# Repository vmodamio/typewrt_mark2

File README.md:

# Typewrt Mark II (ver 2.0)

Typewrt is a modern conception of a digital typewriter, designed as an
instrument for creating literary works without the need of further devices or
software. 
The idea revolves around a mechanical feeling, and it is designed with the
following key aspects:
1) Output: A reflective memory-in-pixel monochrome LCD from SHARP. This is a
4.4" display with a todays low resolution (320x240, QVGA). This resolution is 
enough to produce sharp glyphs using VGA font 8x16 bitmaps. It allows for 15
lines with 40 characters. The readability is exceptional both indoors and
outdoors. Because of the resolution and the ability to perform partial
refreshes, it updates very fast. 

2) Input: A mechanical keyboard with high quality switches and thick PBT
keycaps, arranged in a 60% layout. Mounted in a sturdy brass plate and a custom
made PCB. 
4) Power: Typewrt doesn't produce light. It doesn't stress the eyes. It doesn't
produce heat when you write on the lap. And it does not need a charger around.
The SHARP display is ultra low power. As it does the keyboard and the main
board. 
3) Process: The core of the device, and the main departure from a typewriter or 
a simple drafting device. Typewrt is an embedded vi text editor. It allows to
navigate through the document or documents very efficiently. Manipulate text
with any complexity, and recursively. Do search and replace, etc. You can even
autocomplete words, or perform fuzzy searches. It works natively with utf-8
encoding, and it can change the keyboard layout on the fly to english, spanish,
italian, french, german, norwegian, turkish and colemak.
5) Ergonomics: The design is meant to be robust and stable. The keyboard height
has been minimized. Cherry profile keycups are used, and the keyboard plane is
tilted by 6 degree.  The display distance and viewing angle is kept large
enough to allow long writing sessions. The display is 35 degree respect to the 
horizontal plane. The keyboard has been silenced as much as possible, so you
have a good peace of mind when typing in public places.  The tactility and
response of the keyboard is very conforting. 
6) Remote sync: The device has LE Bluetooth and allows to copy your files to
your phone consuming very little power, and without needing external networks.

The main difference of Typewrt mark II respect to the first iteration is the
hardware. Typewrt-I was built with a single-board-computer, running a ARM based 
linux from which you could run any program on the terminal. 
Typewrt-II doesn't have a computer. There is no terminal or specific drivers for
the keyboard or the display. Keyboard, display and text processor conform a
unique firmware embedded into a ESP32S3 microprocessor. 
Just one application (a modified vi editor with a simple file browser), running 
in a much more constrained environment. 8 MB of ram memory instead of 0.5 GB in
Typewrt-I. 1 MB firmware on flash memory instead of 0.5GB of linux distribution. 
And still, it performs faster, and consumes much less power. 
The interaction with Typewrt-2 is straight. There is no loggins or shells or
passwords. You press the power button and start writing instant on a blank 
document.

# How to:
Because the esp firmware is a submodule repository, clone this project as 
``` 
git clone --recurse-submodules https://github.com/vmodamio/typewrt_mark2.git 
```
The building process might be a long project. Please dont hesitate to ask if you
find difficulties and/or lack of documentation. 
For flashing the firmware, you need the Espressiff IDF installed in your computer.
You can follow [the instructions here for the v6.0](https://docs.espressif.com/projects/esp-idf/en/v6.0.1/esp32s3/get-started/index.html)
Once installed, from the /firmware/esp folder:
``` 
idf.py build
idf.py flash
```

# Firmware:
The text editor has been forked from the [fantastic nextVi](https://github.com/kyx0r/nextvi) 
text editor by Kyryl Melekhin. The editor, originally a terminal program, has been 
adapted to an embedded firmware using the Espressiff IDF, and it runs under FreeRTOS. 
Regarding functionality, the original right-to-left support, all the syntax highlight and 
filetype code, as well as all shell/terminal related code has been removed. 
The program has been adapted to a non-terminal environment, with a custom
keyboard and display interpretation. Additionally, all the functionality related to
files, paths or filesystem in general, has been derived to a more-dedicated filebrowser. 
The filebrowser is in fact the place where you land with the former quit command. 
A battery, memmory and date/time status has been added, as well as a BLE small protocol 
to transfer files.  And last, an special hard-wrap mechanism has been implemented.  

# Hardware:
The machine consists on a feather ESP32s3[d] (unexpected maker) and an Adafruit
adalogger RTC+SD card. The Sharp MIP 4.4" display, is mounted in a custom PCB
that has a 5V booster, and a 7555 timer for the vcom signal (both ultra low
power). The keyboard pcb consists barely on an octal latch SN74HC573A that
drives 8 inputs/outputs. In addition, a power button and a yellow led on the 
enclosure, and a usb-c connector on the back. For the connector, a tiny pcb was
made to pull down the CC1 and CC2 lines with 5.1k. It has also a small jumper to
remove the data lines, in case you dont want someone touching your firmware. 

# Power figures:
Typewrt main display, the SHARP MIP, consumes 50 uA when idle, and 600 uA when
refreshing. It is probably the lowest power display ever. This, considering
that, in many writing divices, the display is by far the most power hungry part.
The keyboard on Typewrt mark I was implemented on a low power STM32
microcontroller, working in interrupt mode and sleeping most of the time, and
sending via uart events. Typewrt mark II is just one microcontroller, doing
exactly the same task as for the keyboard, but for the whole firmware. 
The display vcom signal is hardware produced with the timer, so no task is
needed for the display when the system is idle.
Check the power consumption folder for real measurements.
Machine idle is around 1.4 mA, typing costs 38 mA, and deep sleep 340 uA.

# Vi at a glance:

Vi is one of the main text editors in unix/linux distributions. Its
functionality is divided into three different modes: insert, nomal and ex mode.
Once you are inside vi, you press "i" to enter insert mode, and you can start
typing in your document. Many people hate vi just because this initial
frustration, akwardness responses of the keyboard when you are not in Insert
mode. This is because vi is very powerful. It has many key bindings, and the
learning curve is somehow step. 

In insert mode, it behaves like the simplest text editor you could imagine. As
far as you dont escape, pressing the Esc key, you basically insert characters
in your text buffer. There are very few but useful key bindings in insert mode
however. Press Ctrl-W to delete your last word. Or Ctrl-N to autocomplete a
word you started typing.  To save your text (to write your buffer into a file),
you escape to enter normal mode, then you type ":" to enter ex mode, and "w
<filename>" to write.

Normal mode is where things get fun. In this mode you dont create text by
typing, but instead you type keybindings to manipulate the text you already
have, or navigate throw the buffer/buffers, copy or paste pieces of text into
the buffer, or different registers, search or replace, delete, and many other
things. This editor paradigm works very nice for coding, among other things,
were you would spend considerable part of your time rearranging pieces of text
or modifying functions or variables. For writing fiction I find it equally
useful.  The navigation, or movements, are the first step departing from your
standard, plain editor. The left, right, up and down cursor movements in vi are
arranged in the main keyboard row as h,j,k,l for left, down, up and right. 
That is the main reason you would't need arrow keys in a vi text editor. 
If you get used to this, you wont miss again the arrow keys.  You can move
forward or backwards by words, paragraphs, programmed marks, entire
documents/buffers.
You can concatenate actions with movements, like delete 5 words backwards, or
find character <character> 3 times, to say, or copy text til mark, or
paste register 1...  Pressing "." in normal mode executes the last instruction
again. For example "dB" to delete backwards  to the begining of a word
(including punctuation). Then pressing "." will continue to delete that way.

# Credits:
The text editor is based on the nextVI project (please refer to the firmware folder).
The VGA font is borrowed from the ZAP group, Australia (Copyright (C) 2004–26, John Zaitseff).
The font used for the splash screen is MomoTrustDisplay-Regular.ttf (Google fonts) 
designed by Type Associates, Copyright 2024 The MoMo Trust Display Project Authors. 

# License:
This project is distributed under GPL3 license. Copyright (C) 2026 Victor Modamio

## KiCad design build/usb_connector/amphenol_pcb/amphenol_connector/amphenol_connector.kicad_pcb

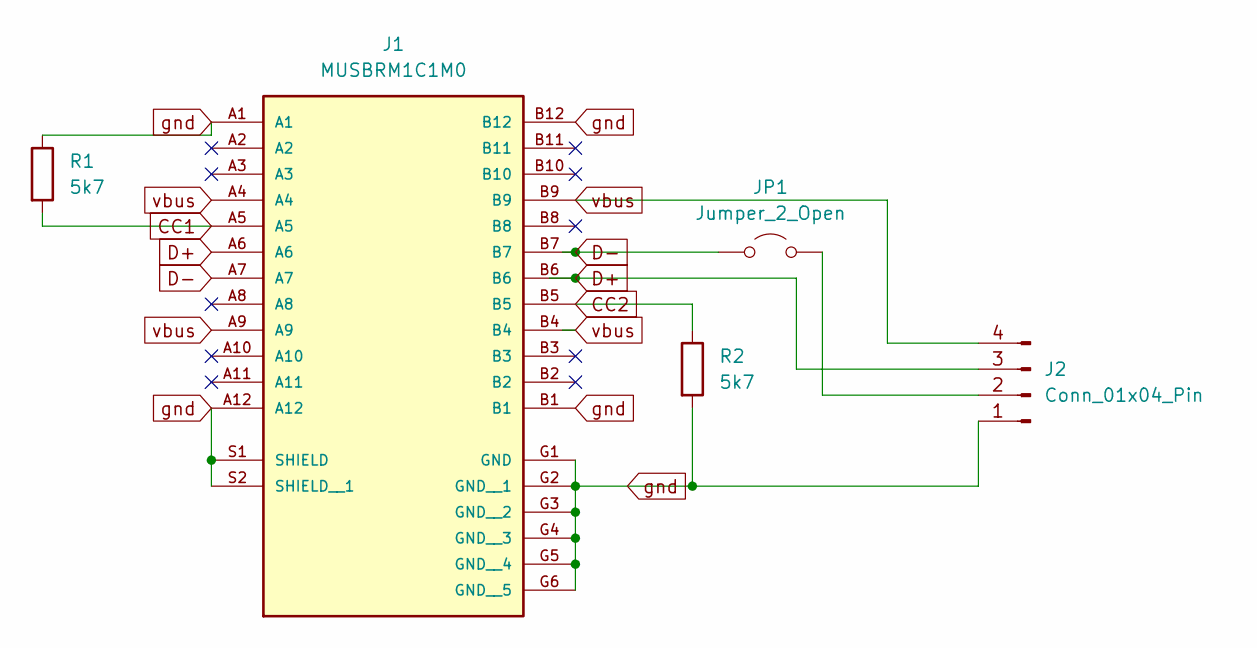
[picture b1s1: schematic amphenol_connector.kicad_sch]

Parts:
J1: MUSBRM1C1M0; AMPHENOL_MUSBRM1C1M0_no_courtyard; PARTREV D
J2: Conn_01x04_Pin; PinHeader_1x04_P1.27mm_Vertical
JP1: Jumper_2_Open; PinHeader_1x02_P1.27mm_Vertical
R1, R2: 5k7; R_1206_3216Metric_Pad1.30x1.75mm_HandSolder

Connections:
CC1: J1.A5, R1.2
CC2: J1.B5, R2.1
D+: J1.A6, J1.B6, J2.3
D-: J1.A7, J1.B7, JP1.1 (A)
unnamed: J2.2, JP1.2 (B)
gnd: J1.A1, J1.A12, J1.B1, J1.B12, J1.G1 (GND), J1.G2 (GND__1), J1.G3 (GND__2), J1.G4 (GND__3), J1.G5 (GND__4), J1.G6 (GND__5), J1.S1 (SHIELD), J1.S2 (SHIELD__1), J2.1, R1.1, R2.2
vbus: J1.A4, J1.A9, J1.B4, J1.B9, J2.4

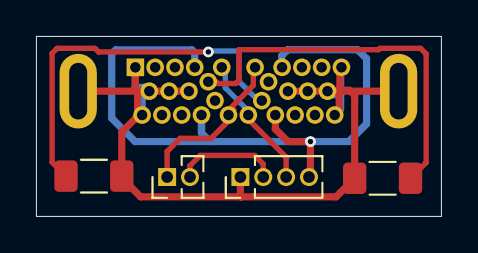
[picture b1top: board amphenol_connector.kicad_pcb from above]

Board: 2 copper layers, 22.5 x 10.0 mm, 5 parts (0 on the bottom side), 7 nets.

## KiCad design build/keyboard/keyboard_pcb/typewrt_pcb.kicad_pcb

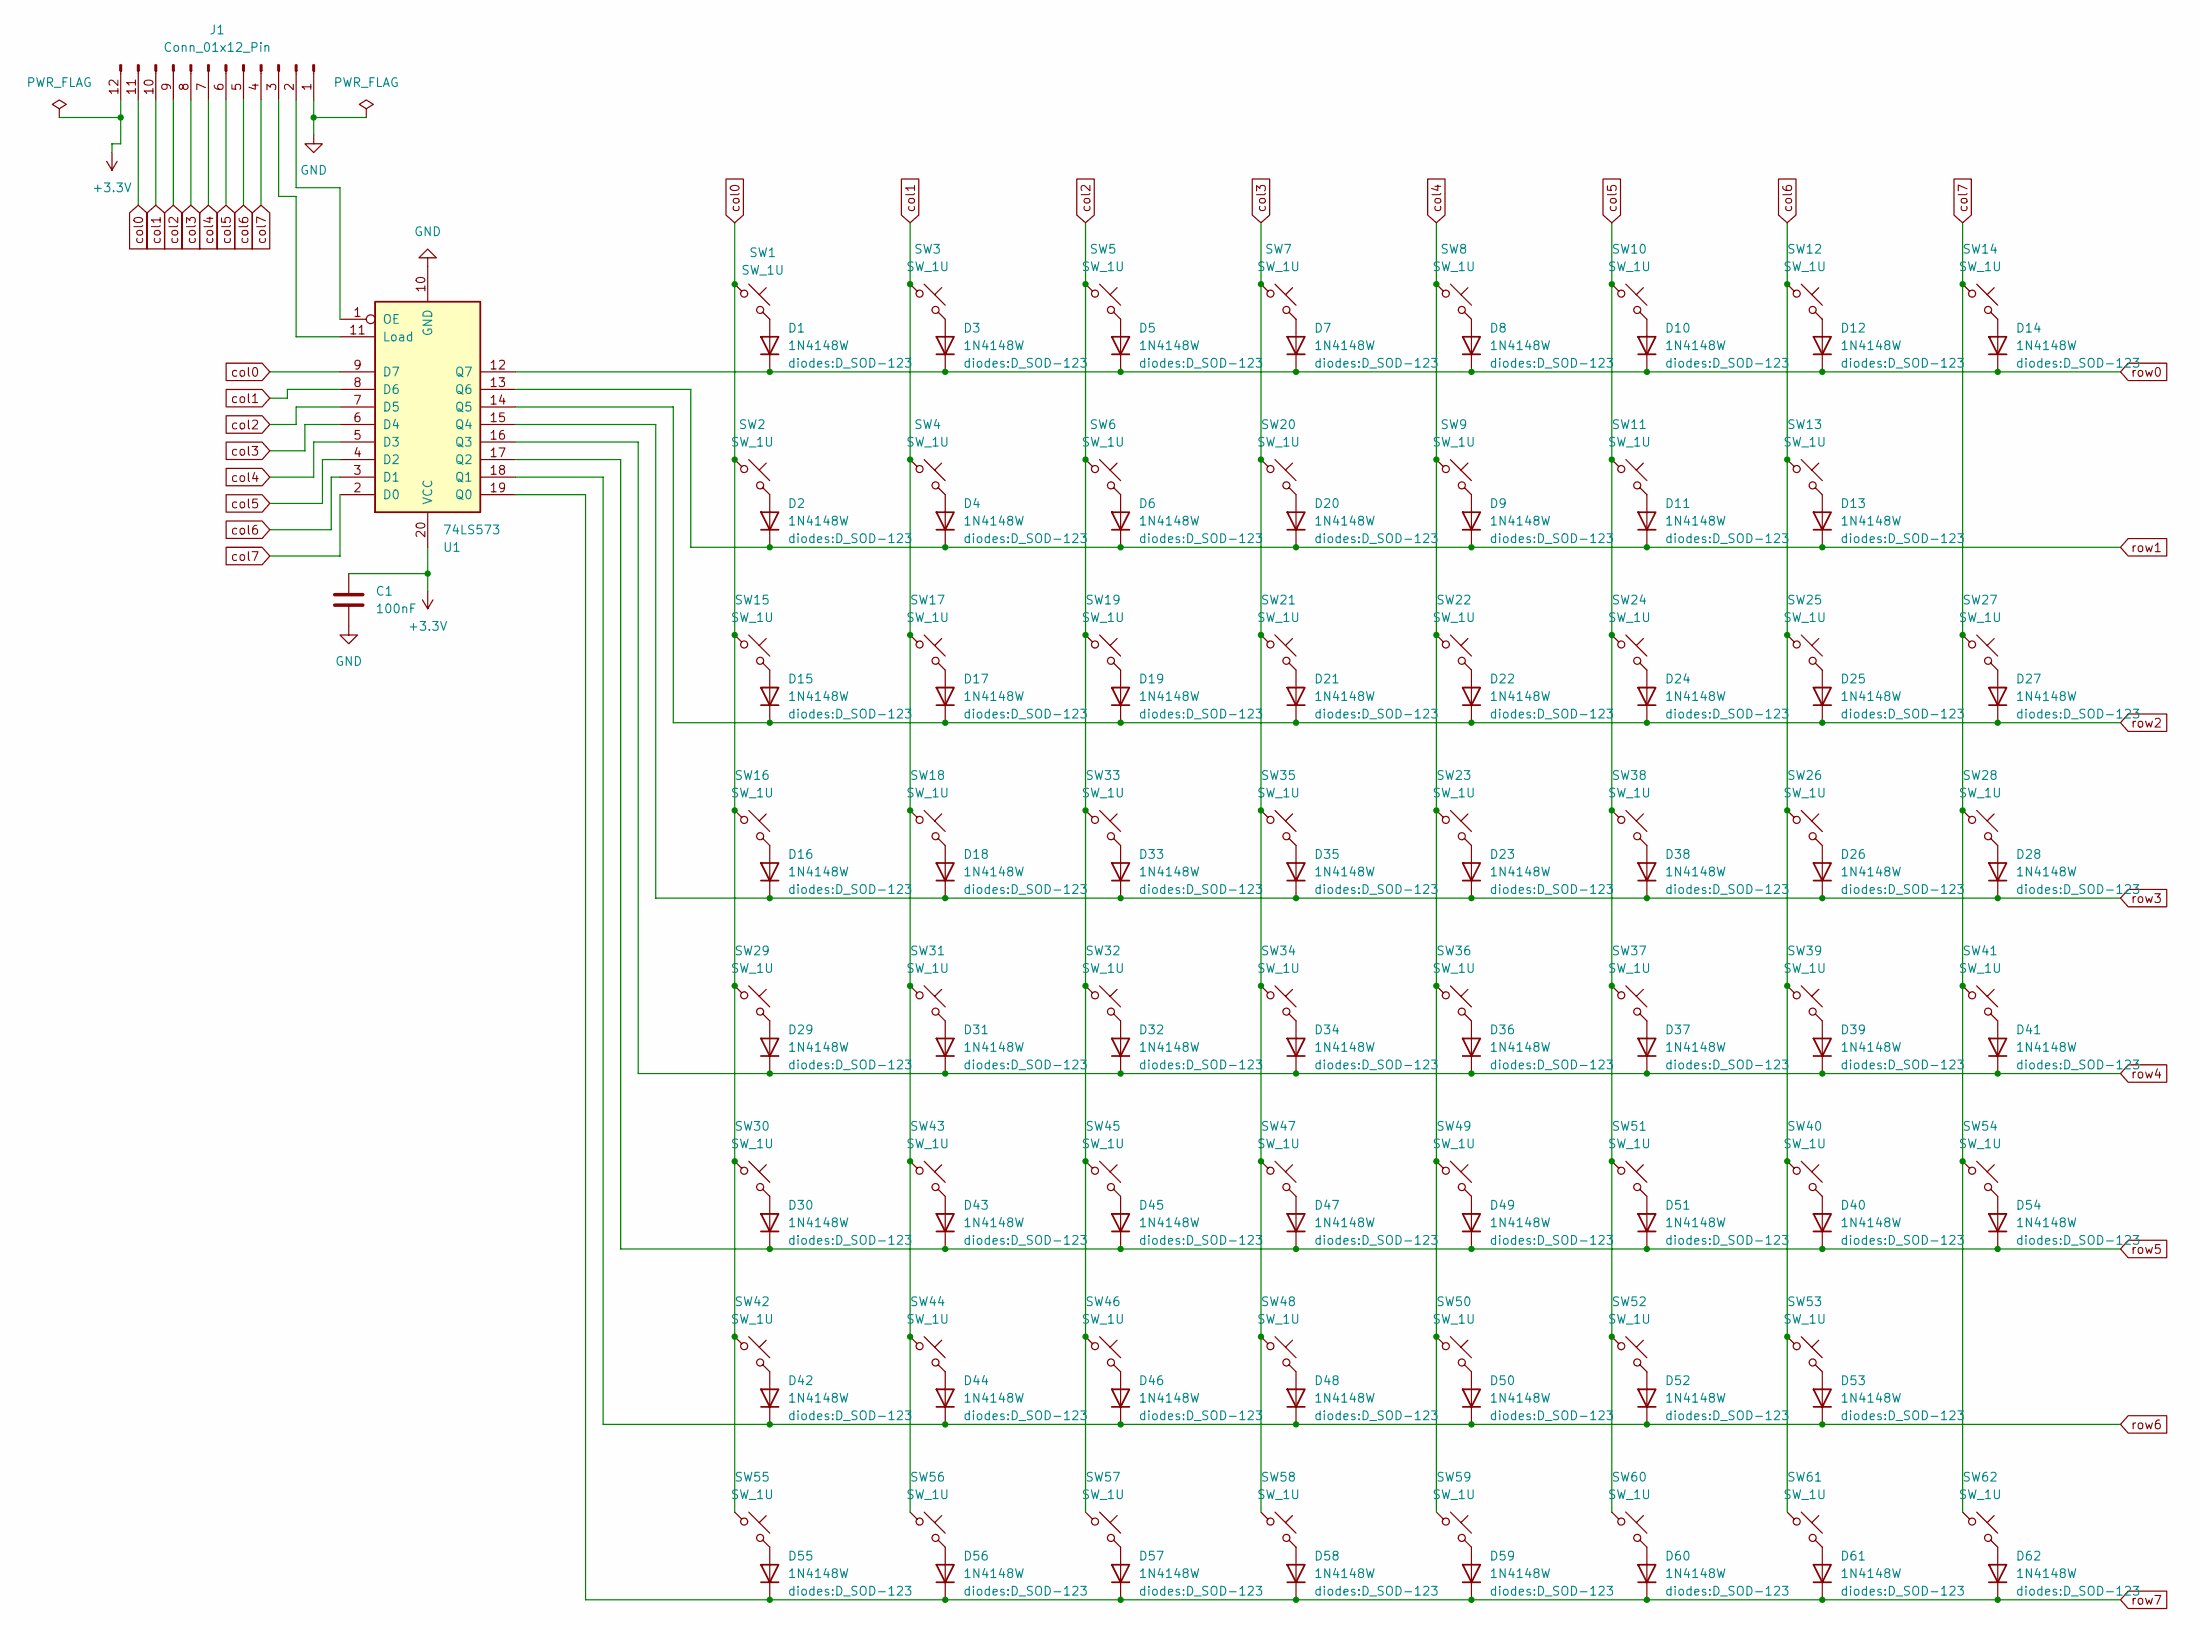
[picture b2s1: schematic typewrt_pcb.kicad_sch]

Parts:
C1: 100nF; C_1206_3216Metric_Pad1.33x1.80mm_HandSolder
D1, D2, D3, D4, D5, D6, D7, D8, D9, D10, D11, D12, D13, D14, D15, D16, D17, D18, D19, D20, D21, D22, D23, D24, D25, D26, D27, D28, D29, D30, D31, D32, D33, D34, D35, D36, D37, D38, D39, D40, D41, D42, D43, D44, D45, D46, D47, D48, D49, D50, D51, D52, D53, D54, D55, D56, D57, D58, D59, D60, D61, D62: 1N4148W; D_SOD-123
J1: Conn_01x12_Pin; PinHeader_1x12_P1.27mm_Vertical
SW1, SW2, SW3, SW4, SW5, SW6, SW7, SW8, SW9, SW10, SW11, SW12, SW13, SW16, SW17, SW18, SW19, SW20, SW21, SW22, SW23, SW24, SW25, SW26, SW27, SW30, SW31, SW32, SW33, SW34, SW35, SW36, SW37, SW38, SW39, SW40, SW41, SW43, SW44, SW45, SW46, SW47, SW48, SW49, SW50, SW51, SW52, SW53: SW_1U; MX-Solderable-1U
SW14: SW_1U; MX-Solderable-2U
SW15: SW_1U; MX-Solderable-1.5U
SW28: SW_1U; MX-Solderable-ISO
SW29: SW_1U; MX-Solderable-1.75U
SW42, SW55, SW56, SW57, SW59, SW60, SW61, SW62: SW_1U; MX-Solderable-1.25U
SW54: SW_1U; MX-Solderable-2.75U
SW58: SW_1U; MX-Solderable-6.25U-ReversedStabilizers
U1: 74LS573; DIP-20_W7.62mm

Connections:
+3.3V: C1.1, J1.12, U1.20 (VCC)
GND: C1.2, J1.1, U1.10 (GND)
unnamed: D1.2 (A), SW1.2
unnamed: D2.2 (A), SW2.2
unnamed: D3.2 (A), SW3.2
unnamed: D4.2 (A), SW4.2
unnamed: D5.2 (A), SW5.2
unnamed: D6.2 (A), SW6.2
unnamed: D7.2 (A), SW7.2
unnamed: D8.2 (A), SW8.2
unnamed: D9.2 (A), SW9.2
unnamed: D10.2 (A), SW10.2
unnamed: D11.2 (A), SW11.2
unnamed: D12.2 (A), SW12.2
unnamed: D13.2 (A), SW13.2
unnamed: D14.2 (A), SW14.2
unnamed: D15.2 (A), SW15.2
unnamed: D16.2 (A), SW16.2
unnamed: D17.2 (A), SW17.2
unnamed: D18.2 (A), SW18.2
unnamed: D19.2 (A), SW19.2
unnamed: D20.2 (A), SW20.2
unnamed: D21.2 (A), SW21.2
unnamed: D22.2 (A), SW22.2
unnamed: D23.2 (A), SW23.2
unnamed: D24.2 (A), SW24.2
unnamed: D25.2 (A), SW25.2
unnamed: D26.2 (A), SW26.2
unnamed: D27.2 (A), SW27.2
unnamed: D28.2 (A), SW28.2
unnamed: D29.2 (A), SW29.2
unnamed: D30.2 (A), SW30.2
unnamed: D31.2 (A), SW31.2
unnamed: D32.2 (A), SW32.2
unnamed: D33.2 (A), SW33.2
unnamed: D34.2 (A), SW34.2
unnamed: D35.2 (A), SW35.2
unnamed: D36.2 (A), SW36.2
unnamed: D37.2 (A), SW37.2
unnamed: D38.2 (A), SW38.2
unnamed: D39.2 (A), SW39.2
unnamed: D40.2 (A), SW40.2
unnamed: D41.2 (A), SW41.2
unnamed: D42.2 (A), SW42.2
unnamed: D43.2 (A), SW43.2
unnamed: D44.2 (A), SW44.2
unnamed: D45.2 (A), SW45.2
unnamed: D46.2 (A), SW46.2
unnamed: D47.2 (A), SW47.2
unnamed: D48.2 (A), SW48.2
unnamed: D49.2 (A), SW49.2
unnamed: D50.2 (A), SW50.2
unnamed: D51.2 (A), SW51.2
unnamed: D52.2 (A), SW52.2
unnamed: D53.2 (A), SW53.2
unnamed: D54.2 (A), SW54.2
unnamed: D55.2 (A), SW55.2
unnamed: D56.2 (A), SW56.2
unnamed: D57.2 (A), SW57.2
unnamed: D58.2 (A), SW58.2
unnamed: D59.2 (A), SW59.2
unnamed: D60.2 (A), SW60.2
unnamed: D61.2 (A), SW61.2
unnamed: D62.2 (A), SW62.2
unnamed: J1.2, U1.1 (OE)
unnamed: J1.3, U1.11 (Load)
col0: J1.11, SW1.1, SW2.1, SW15.1, SW16.1, SW29.1, SW30.1, SW42.1, SW55.1, U1.9 (D7)
col1: J1.10, SW3.1, SW4.1, SW17.1, SW18.1, SW31.1, SW43.1, SW44.1, SW56.1, U1.8 (D6)
col2: J1.9, SW5.1, SW6.1, SW19.1, SW32.1, SW33.1, SW45.1, SW46.1, SW57.1, U1.7 (D5)
col3: J1.8, SW7.1, SW20.1, SW21.1, SW34.1, SW35.1, SW47.1, SW48.1, SW58.1, U1.6 (D4)
col4: J1.7, SW8.1, SW9.1, SW22.1, SW23.1, SW36.1, SW49.1, SW50.1, SW59.1, U1.5 (D3)
col5: J1.6, SW10.1, SW11.1, SW24.1, SW37.1, SW38.1, SW51.1, SW52.1, SW60.1, U1.4 (D2)
col6: J1.5, SW12.1, SW13.1, SW25.1, SW26.1, SW39.1, SW40.1, SW53.1, SW61.1, U1.3 (D1)
col7: J1.4, SW14.1, SW27.1, SW28.1, SW41.1, SW54.1, SW62.1, U1.2 (D0)
row0: D1.1 (K), D3.1 (K), D5.1 (K), D7.1 (K), D8.1 (K), D10.1 (K), D12.1 (K), D14.1 (K), U1.12 (Q7)
row1: D2.1 (K), D4.1 (K), D6.1 (K), D9.1 (K), D11.1 (K), D13.1 (K), D20.1 (K), U1.13 (Q6)
row2: D15.1 (K), D17.1 (K), D19.1 (K), D21.1 (K), D22.1 (K), D24.1 (K), D25.1 (K), D27.1 (K), U1.14 (Q5)
row3: D16.1 (K), D18.1 (K), D23.1 (K), D26.1 (K), D28.1 (K), D33.1 (K), D35.1 (K), D38.1 (K), U1.15 (Q4)
row4: D29.1 (K), D31.1 (K), D32.1 (K), D34.1 (K), D36.1 (K), D37.1 (K), D39.1 (K), D41.1 (K), U1.16 (Q3)
row5: D30.1 (K), D40.1 (K), D43.1 (K), D45.1 (K), D47.1 (K), D49.1 (K), D51.1 (K), D54.1 (K), U1.17 (Q2)
row6: D42.1 (K), D44.1 (K), D46.1 (K), D48.1 (K), D50.1 (K), D52.1 (K), D53.1 (K), U1.18 (Q1)
row7: D55.1 (K), D56.1 (K), D57.1 (K), D58.1 (K), D59.1 (K), D60.1 (K), D61.1 (K), D62.1 (K), U1.19 (Q0)

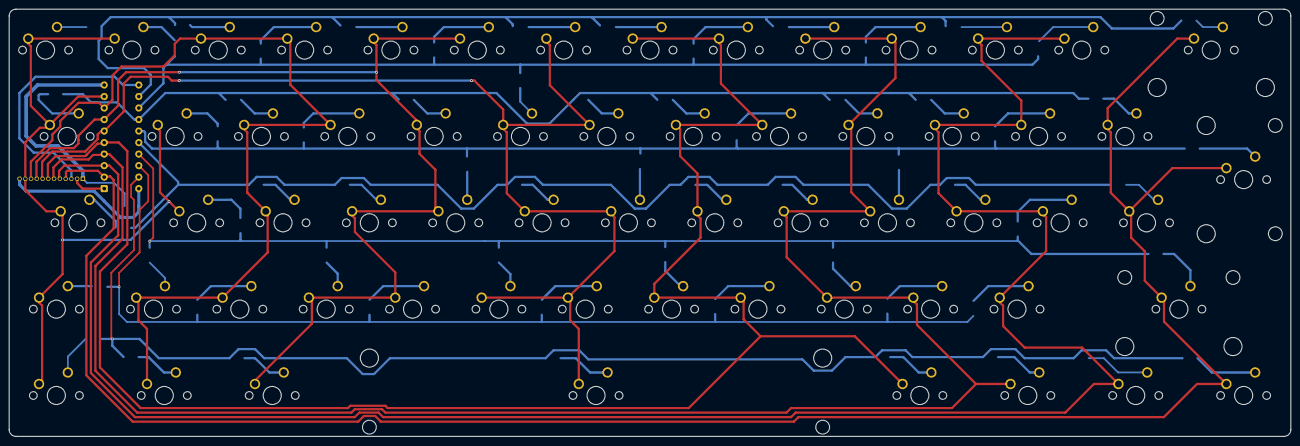
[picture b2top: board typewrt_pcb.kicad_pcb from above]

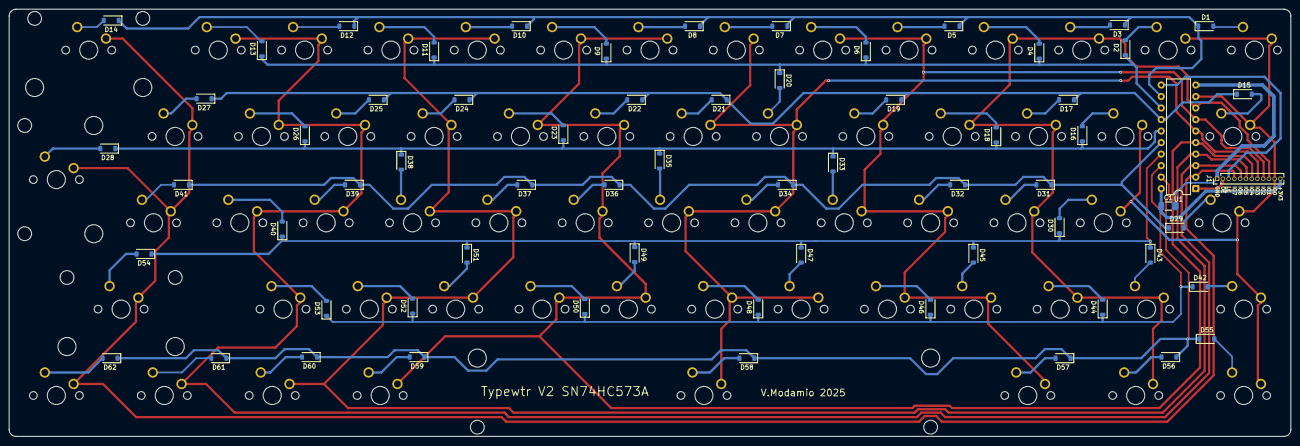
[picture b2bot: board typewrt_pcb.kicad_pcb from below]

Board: 2 copper layers, 282.8 x 94.2 mm, 127 parts (65 on the bottom side), 82 nets.

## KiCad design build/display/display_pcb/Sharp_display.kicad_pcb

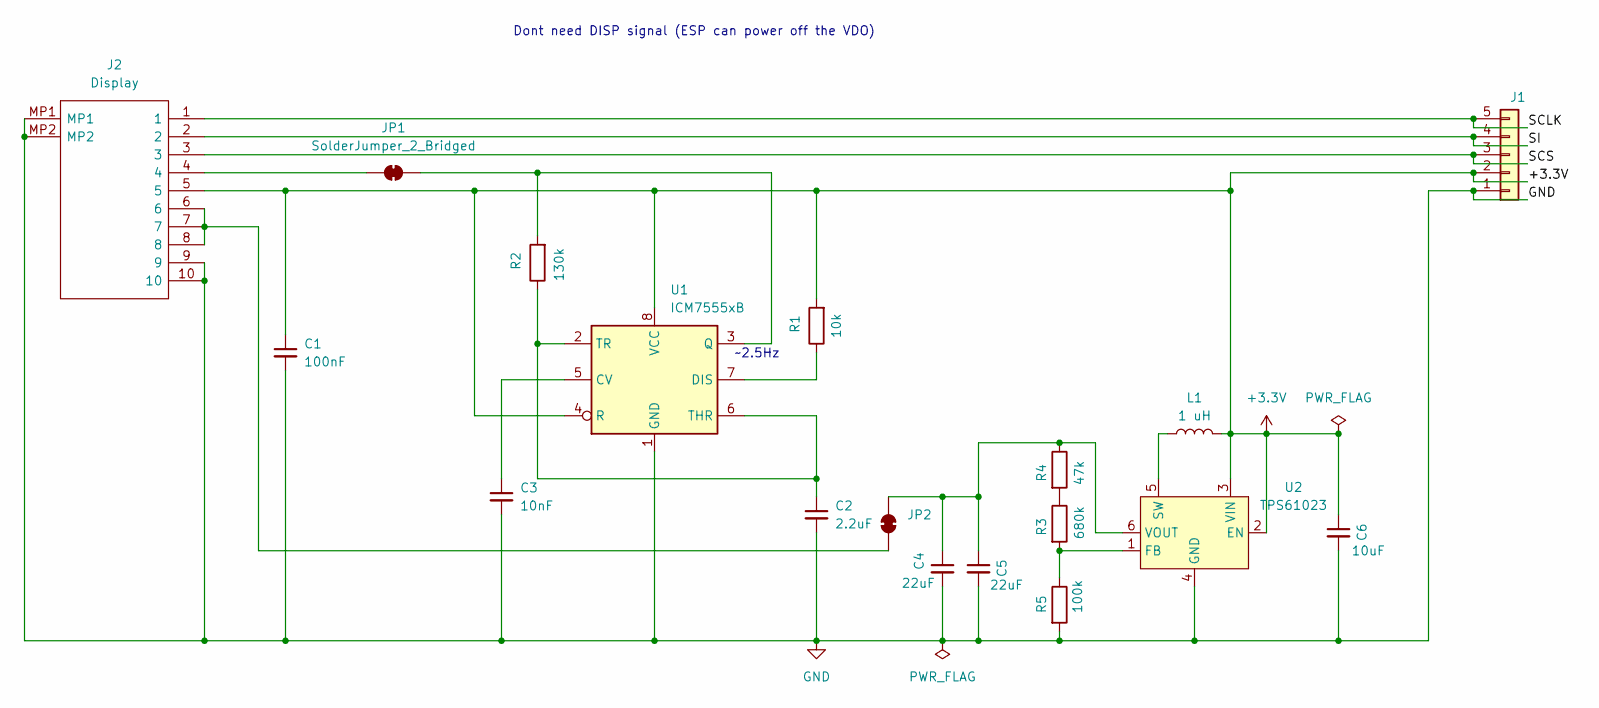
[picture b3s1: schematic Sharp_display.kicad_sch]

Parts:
C1: 100nF; C_1206_3216Metric_Pad1.33x1.80mm_HandSolder
C2: 2.2uF; C_1206_3216Metric_Pad1.33x1.80mm_HandSolder
C3: 10nF; C_1206_3216Metric_Pad1.33x1.80mm_HandSolder
C4, C5: 22uF; C_1206_3216Metric_Pad1.33x1.80mm_HandSolder
C6: 10uF; C_1206_3216Metric_Pad1.33x1.80mm_HandSolder
J1: Conn_01x05; PinHeader_1x05_P2.54mm_Vertical
J2: Display; GCT_FFC2B35-10-G_REVA2; Manufacturer_Part_Number 5051101092; Mouser Part Number N/A
JP1, JP2: SolderJumper_2_Bridged; SolderJumper-2_P1.3mm_Bridged2Bar_Pad1.0x1.5mm
L1: 1 uH; L_Wurth_WE-LQSH-4020
R1: 10k; R_1206_3216Metric_Pad1.30x1.75mm_HandSolder
R2: 130k; R_1206_3216Metric_Pad1.30x1.75mm_HandSolder
R3: 680k; R_1206_3216Metric_Pad1.30x1.75mm_HandSolder
R4: 47k; R_1206_3216Metric_Pad1.30x1.75mm_HandSolder
R5: 100k; R_1206_3216Metric_Pad1.30x1.75mm_HandSolder
U1: ICM7555xB; SOIC127P600X175-8N
U2: TPS61023; SOT-563

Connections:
+3.3V: C1.1, C6.1, J1.2, J2.5, L1.2, R1.2, U1.4 (R), U1.8 (VCC), U2.2 (EN), U2.3 (VIN)
/SCLK: J1.5, J2.1
/SCS: J1.3, J2.3
/SI: J1.4, J2.2
GND: C1.2, C2.2, C3.2, C4.2, C5.2, C6.2, J1.1, J2.9, J2.10, J2.MP1, J2.MP2, R5.2, U1.1 (GND), U2.4 (GND)
unnamed 5: J2.4, JP1.1 (A); also elsewhere on the board
unnamed: JP1.2 (B), R2.2, U1.3 (Q)
unnamed 7: J2.6, J2.7, J2.8, JP2.1 (A); also elsewhere on the board
unnamed: C4.1, C5.1, JP2.2 (B), R4.1, U2.6 (VOUT)
unnamed: R3.1, R4.2
unnamed: C3.1, U1.5 (CV)
unnamed: R1.1, U1.7 (DIS)
unnamed: C2.1, R2.1, U1.2 (TR), U1.6 (THR)
unnamed: R3.2, R5.1, U2.1 (FB)
unnamed: L1.1, U2.5 (SW)

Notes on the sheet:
~2.5Hz
Dont need DISP signal (ESP can power off the VDO)

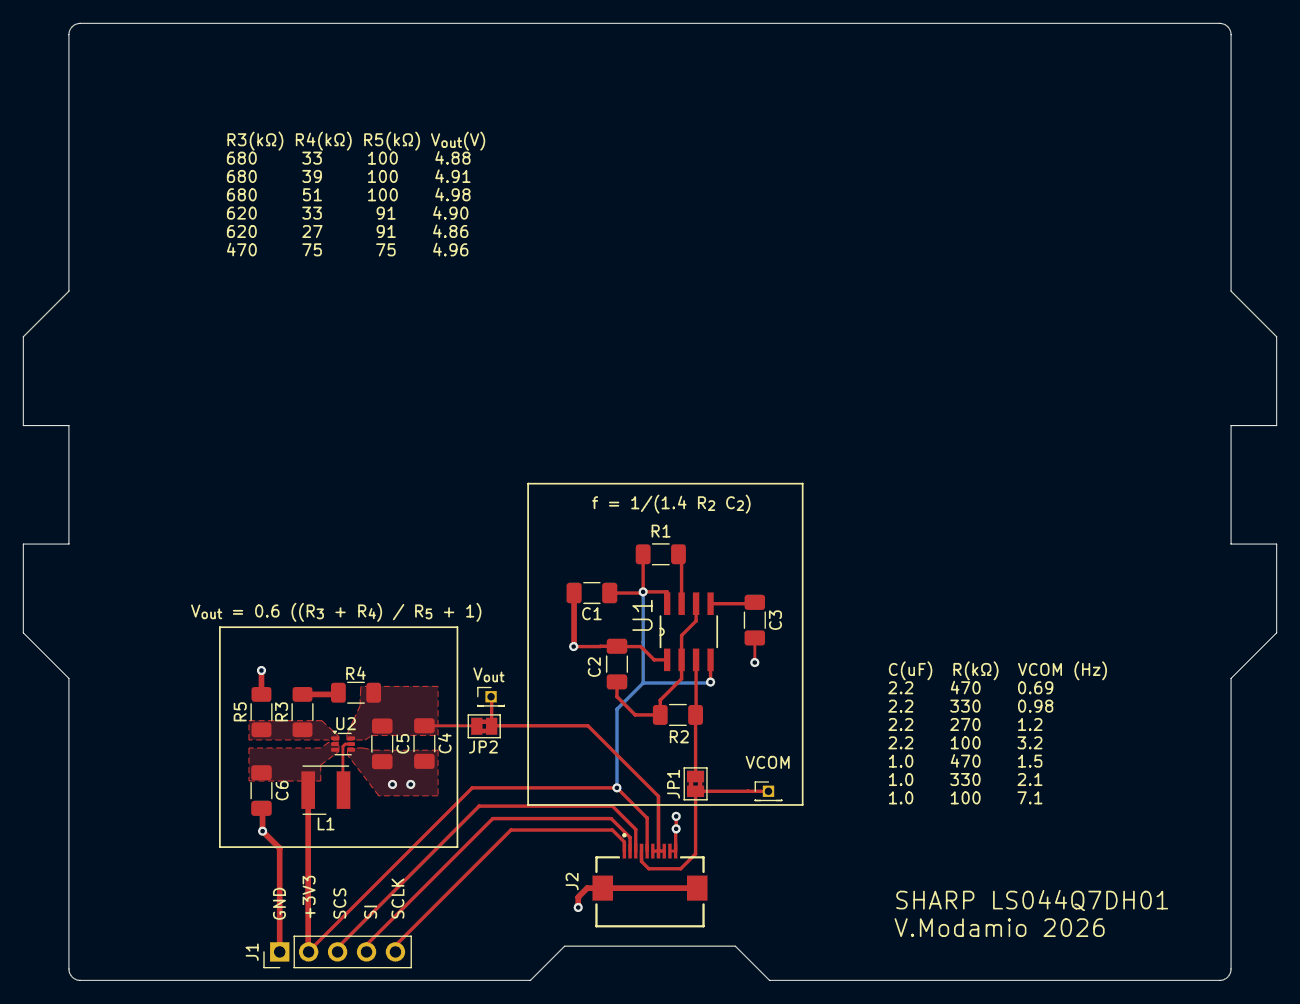
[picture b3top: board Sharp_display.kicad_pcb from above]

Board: 2 copper layers, 110.0 x 84.0 mm, 20 parts (0 on the bottom side), 15 nets.

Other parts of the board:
VCOM: PinHeader_1x01_P1.27mm_Vertical
V_{out}: PinHeader_1x01_P1.27mm_Vertical

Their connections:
unnamed 5: VCOM.1; also elsewhere on the board
unnamed 7: V_{out}.1; also elsewhere on the board

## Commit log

2026-05-22 Update LICENSE with new copyright information
    Added copyright notice for 2026 Victor Modamio.
2026-05-22 First structure of the project
2026-05-22 Added font info
2026-05-22 Add submodule [esp-firmware]
2026-05-22 list of materials
2026-06-04 add pcbs plate
2026-06-05 add enclosure
2026-06-06 Add google font
2026-06-06 add power figures
2026-06-06 add ZAP font John Zaitseff
2026-06-14 starting README
2026-06-14 readme up
2026-06-15 add documentation
2026-06-15 add images
2026-06-15 add copyright in readme
